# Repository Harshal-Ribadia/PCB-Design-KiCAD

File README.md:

Arduino Nano Control Board

This project is a KiCad 9.0 PCB design for a simple control board based on the Arduino Nano.
It integrates an LCD display, I²C communication header, user input buttons, and an LED indicator, making it suitable for small embedded systems and learning projects.

Features

Arduino Nano socket (THT) — easy placement and replacement of the Nano module.

LCD display header (custom footprint, THT) — simple connection to a standard character LCD.

I²C header (custom footprint, THT) — breakout for SCL and SDA lines, enabling easy expansion with sensors and modules.

User interface components:

1 × LED (status indicator).

3 × push buttons (user inputs).

Design Details

Designed in KiCad 9.0 using the Footprint Editor for custom connectors.

All components are through-hole (THT) for easier prototyping and soldering.

Clear layout intended for beginners to practice PCB design, fabrication, and assembly.

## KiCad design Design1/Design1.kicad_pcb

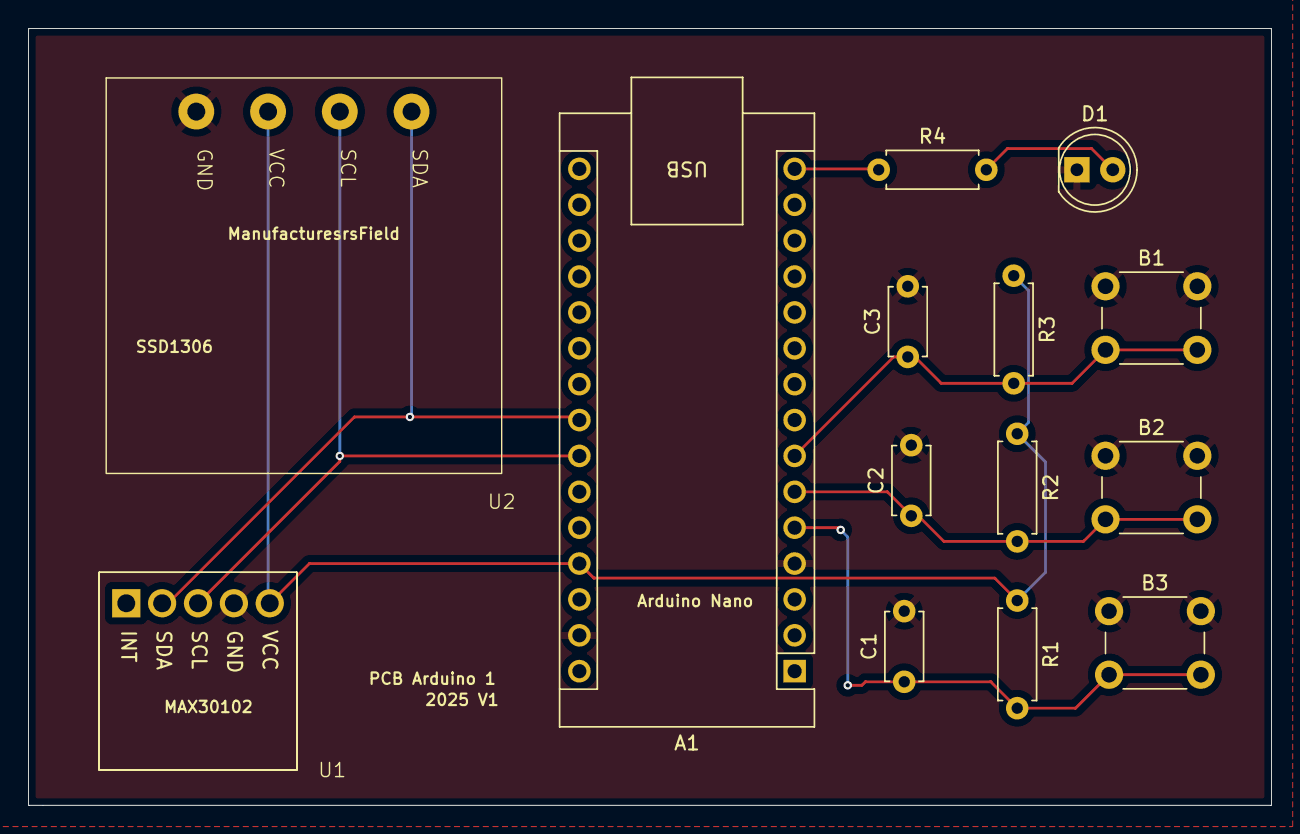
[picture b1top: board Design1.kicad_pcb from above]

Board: 4 copper layers, 88.0 x 55.0 mm, 14 parts (0 on the bottom side), 9 nets.

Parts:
A1: Arduino_Nano_v3.x; Arduino_Nano
B1, B2, B3: SW_Push; SW_PUSH_6mm
C1, C2, C3: 100n; C_Disc_D4.7mm_W2.5mm_P5.00mm
D1: LED; LED_D5.0mm
R1, R2, R3, R4: 1k; R_Axial_DIN0207_L6.3mm_D2.5mm_P7.62mm_Horizontal
U1: Max30102; MAX30102
U2: SSD1306; SSD

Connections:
+5V: A1.27 (+5V), R1.1, R2.1, R3.1, U1.5 (VCC), U2.2 (VCC)
GND: A1.4 (GND), A1.29 (GND), B1.1, B2.1, B3.1, C1.2, C2.2, C3.2, D1.1 (K), U1.4 (GND), U2.1 (GND)
unnamed: A1.23 (A4), U1.2 (SDA), U2.4 (SDA)
unnamed: A1.24 (A5), U1.3 (SCL), U2.3 (SCL)
unnamed: A1.5 (D2), B3.2, C1.1, R1.2
unnamed: A1.6 (D3), B2.2, C2.1, R2.2
unnamed: A1.7 (D4), B1.2, C3.1, R3.2
unnamed: A1.15 (D12), R4.1
unnamed: D1.2 (A), R4.2
